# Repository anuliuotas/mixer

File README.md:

TODO:

### KiCad:
- MixerController: Bad mosfet footprint G and D pins are mixed up
- All: Mounting holes should be grounded
- All: Pinout should be visible at least in drawings layer

### ESPHome
- MixerController: VESC temperature sensor reading from CAN
- MixerInterface: Loading splash screen

### CAD
- Increase height of WAGO holder for more cable space

### Other
- Buy standoffs for VESC cover holder
- Check replacement parts

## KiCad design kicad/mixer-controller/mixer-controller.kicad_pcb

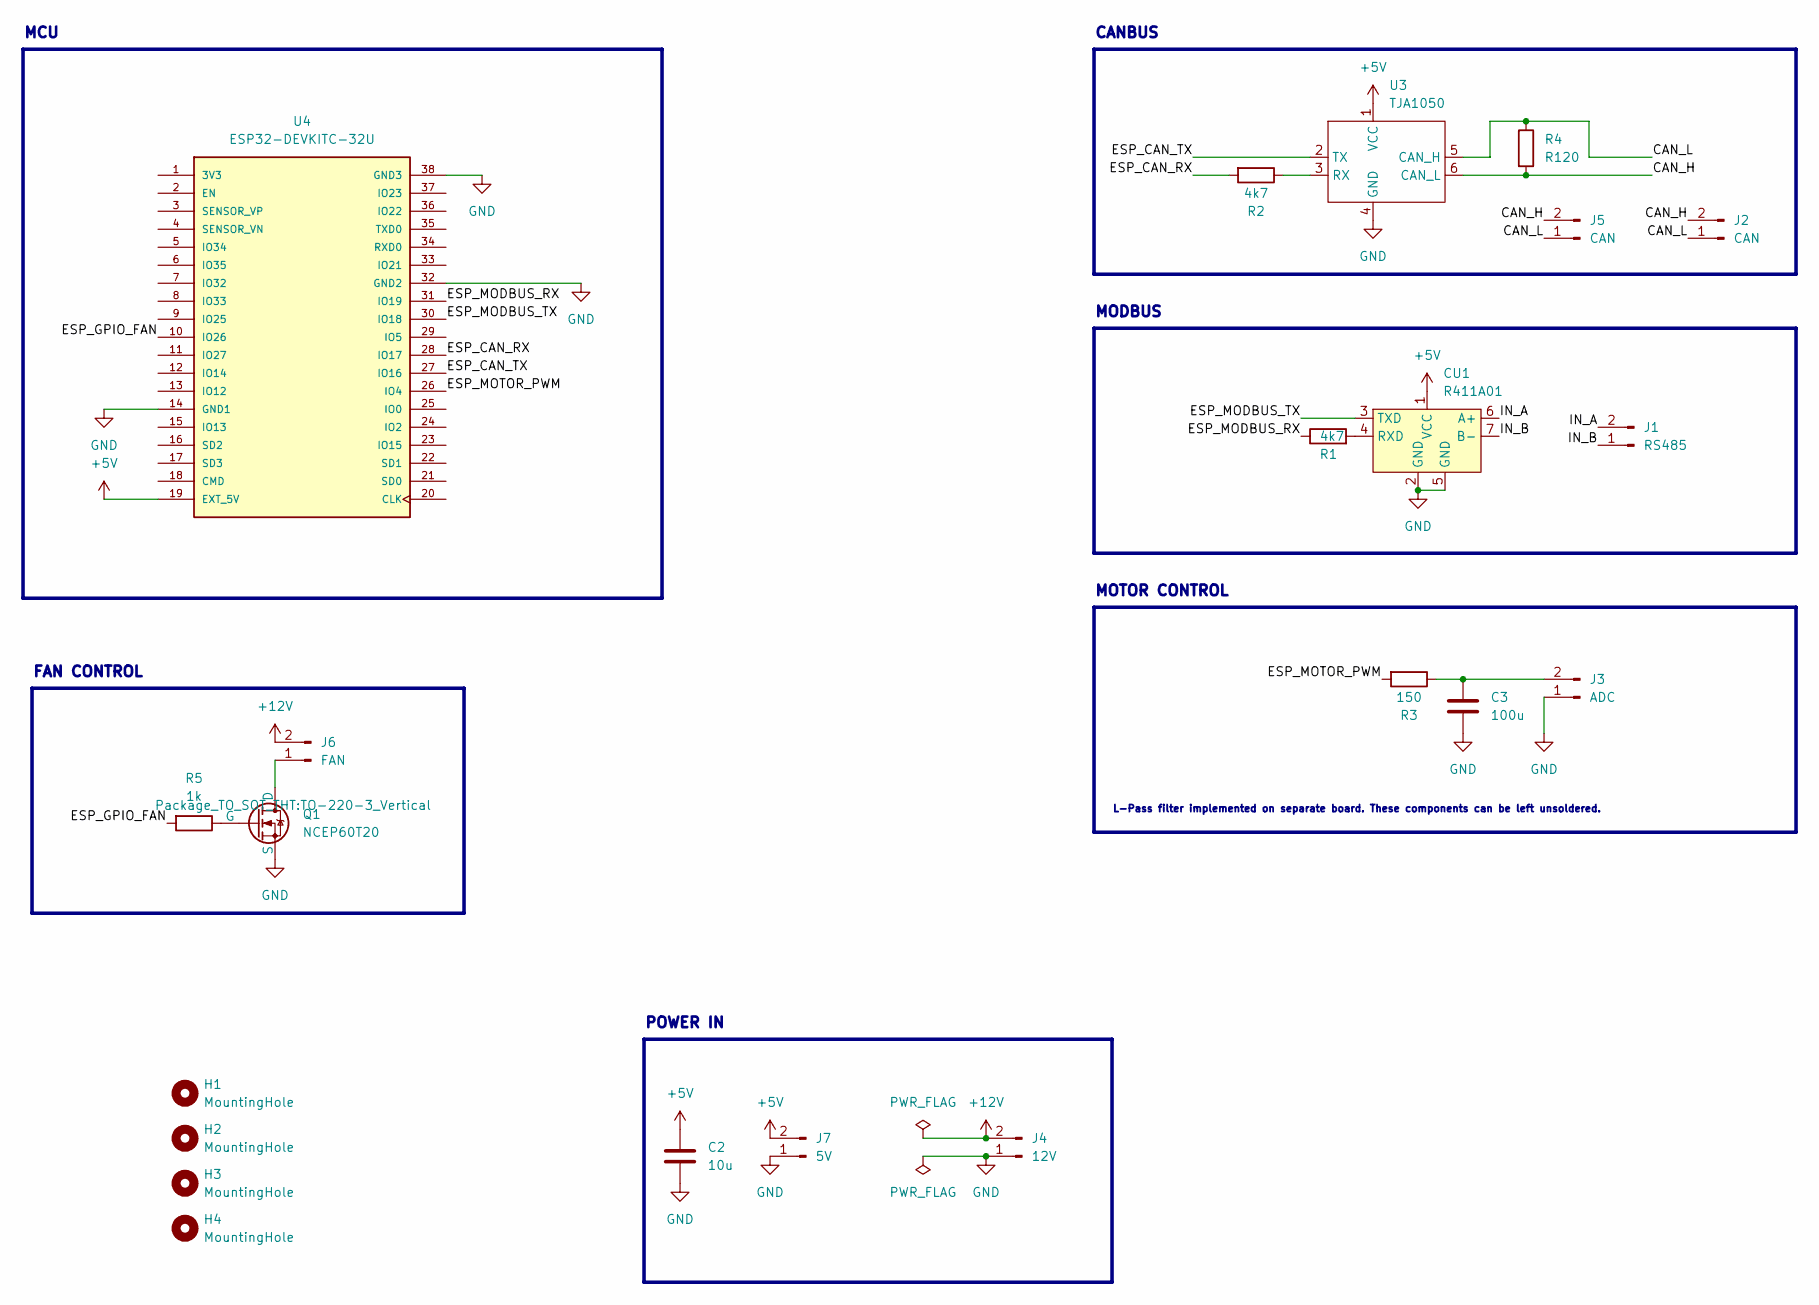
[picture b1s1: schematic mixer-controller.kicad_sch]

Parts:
C2: 10u; C_0805_2012Metric
C3: 100u; C_0805_2012Metric
CU1: R411A01
H1, H2, H3, H4: MountingHole; MountingHole_3.2mm_M3_Pad_Via
J1: RS485; JST_XH_B2B-XH-A_1x02_P2.50mm_Vertical
J2, J5: CAN; JST_XH_B2B-XH-A_1x02_P2.50mm_Vertical
J3: ADC; JST_XH_B2B-XH-A_1x02_P2.50mm_Vertical
J4: 12V; JST_XH_B2B-XH-A_1x02_P2.50mm_Vertical
J6: FAN; JST_XH_B2B-XH-A_1x02_P2.50mm_Vertical
J7: 5V; JST_XH_B2B-XH-A_1x02_P2.50mm_Vertical
Q1: NCEP60T20; TO-220-3_Vertical
R1: 4k7; R_0805_2012Metric
R2: 4k7; R_0805_2012Metric_Pad1.20x1.40mm_HandSolder
R3: 150; R_0805_2012Metric_Pad1.20x1.40mm_HandSolder
R4: R120; R_0805_2012Metric_Pad1.20x1.40mm_HandSolder
R5: 1k; R_0805_2012Metric_Pad1.20x1.40mm_HandSolder
U3: TJA1050
U4: ESP32-DEVKITC-32U; MODULE_ESP32-DEVKITC-32U; PARTREV N/A

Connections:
+5V: C2.1, CU1.1 (VCC), J7.2, U3.1 (VCC), U4.19 (EXT_5V)
+12V: J4.2, J6.2
/CAN_H: J2.2, J5.2, R4.2, U3.6 (CAN_L)
/CAN_L: J2.1, J5.1, R4.1, U3.5 (CAN_H)
/ESP_CAN_RX: R2.2, U4.28 (IO17)
/ESP_CAN_TX: U3.2 (TX), U4.27 (IO16)
/ESP_GPIO_FAN: R5.2, U4.10 (IO26)
/ESP_MODBUS_RX: R1.1, U4.31 (IO19)
/ESP_MODBUS_TX: CU1.3 (TXD), U4.30 (IO18)
/ESP_MOTOR_PWM: R3.2, U4.26 (IO4)
/IN_A: CU1.6 (A+), J1.2
/IN_B: CU1.7 (B-), J1.1
GND: C2.2, C3.2, CU1.2 (GND), CU1.5 (GND), J3.1, J4.1, J7.1, Q1.3 (S), U3.4 (GND), U4.14 (GND1), U4.32 (GND2), U4.38 (GND3)
unnamed: CU1.4 (RXD), R1.2
unnamed: C3.1, J3.2, R3.1
unnamed: J6.1, Q1.1 (D)
unnamed: Q1.2 (G), R5.1
unnamed: R2.1, U3.3 (RX)

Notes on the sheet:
POWER IN
FAN CONTROL
MODBUS
MCU
MOTOR CONTROL
L-Pass filter implemented on separate board. These components can be left unsoldered.
CANBUS

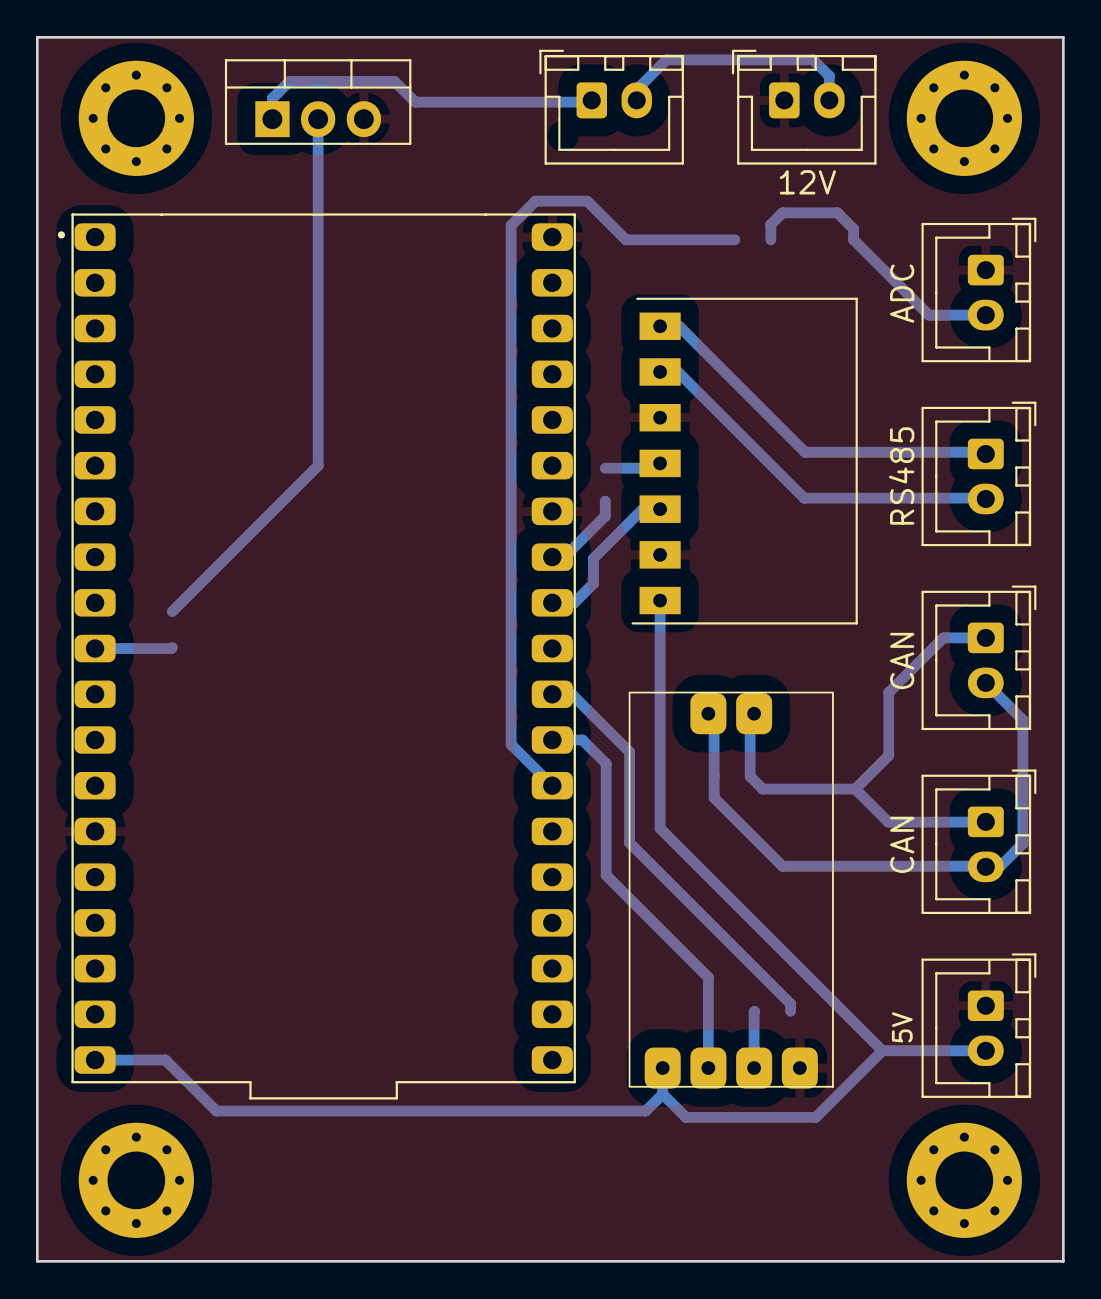
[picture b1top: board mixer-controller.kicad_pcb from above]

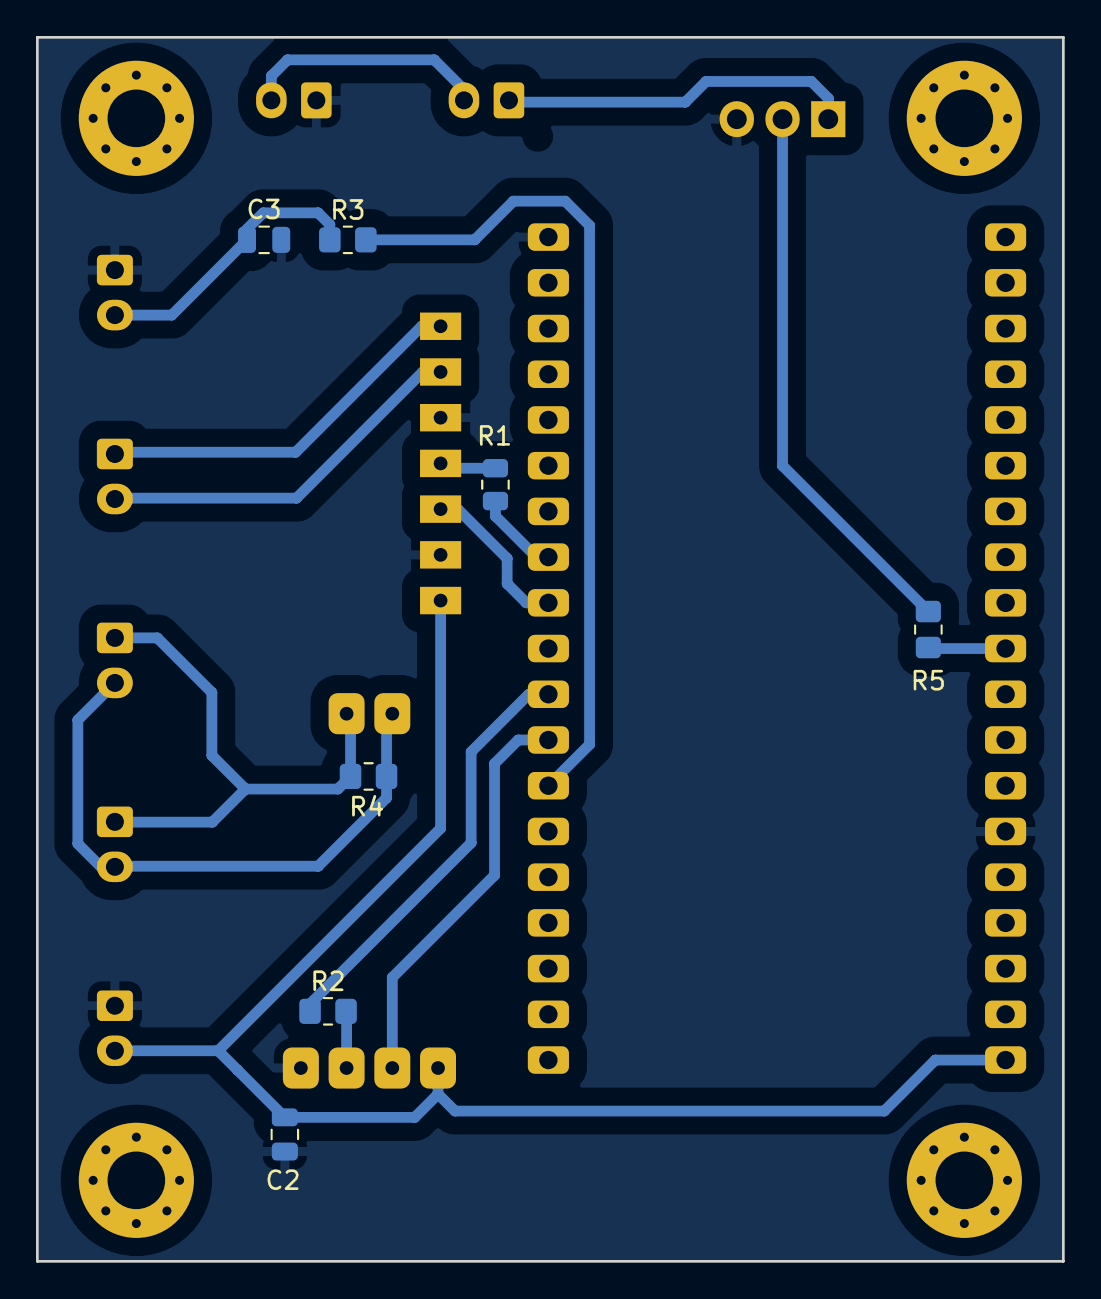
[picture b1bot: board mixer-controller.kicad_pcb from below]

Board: 2 copper layers, 57.0 x 68.0 mm, 22 parts (7 on the bottom side), 18 nets.

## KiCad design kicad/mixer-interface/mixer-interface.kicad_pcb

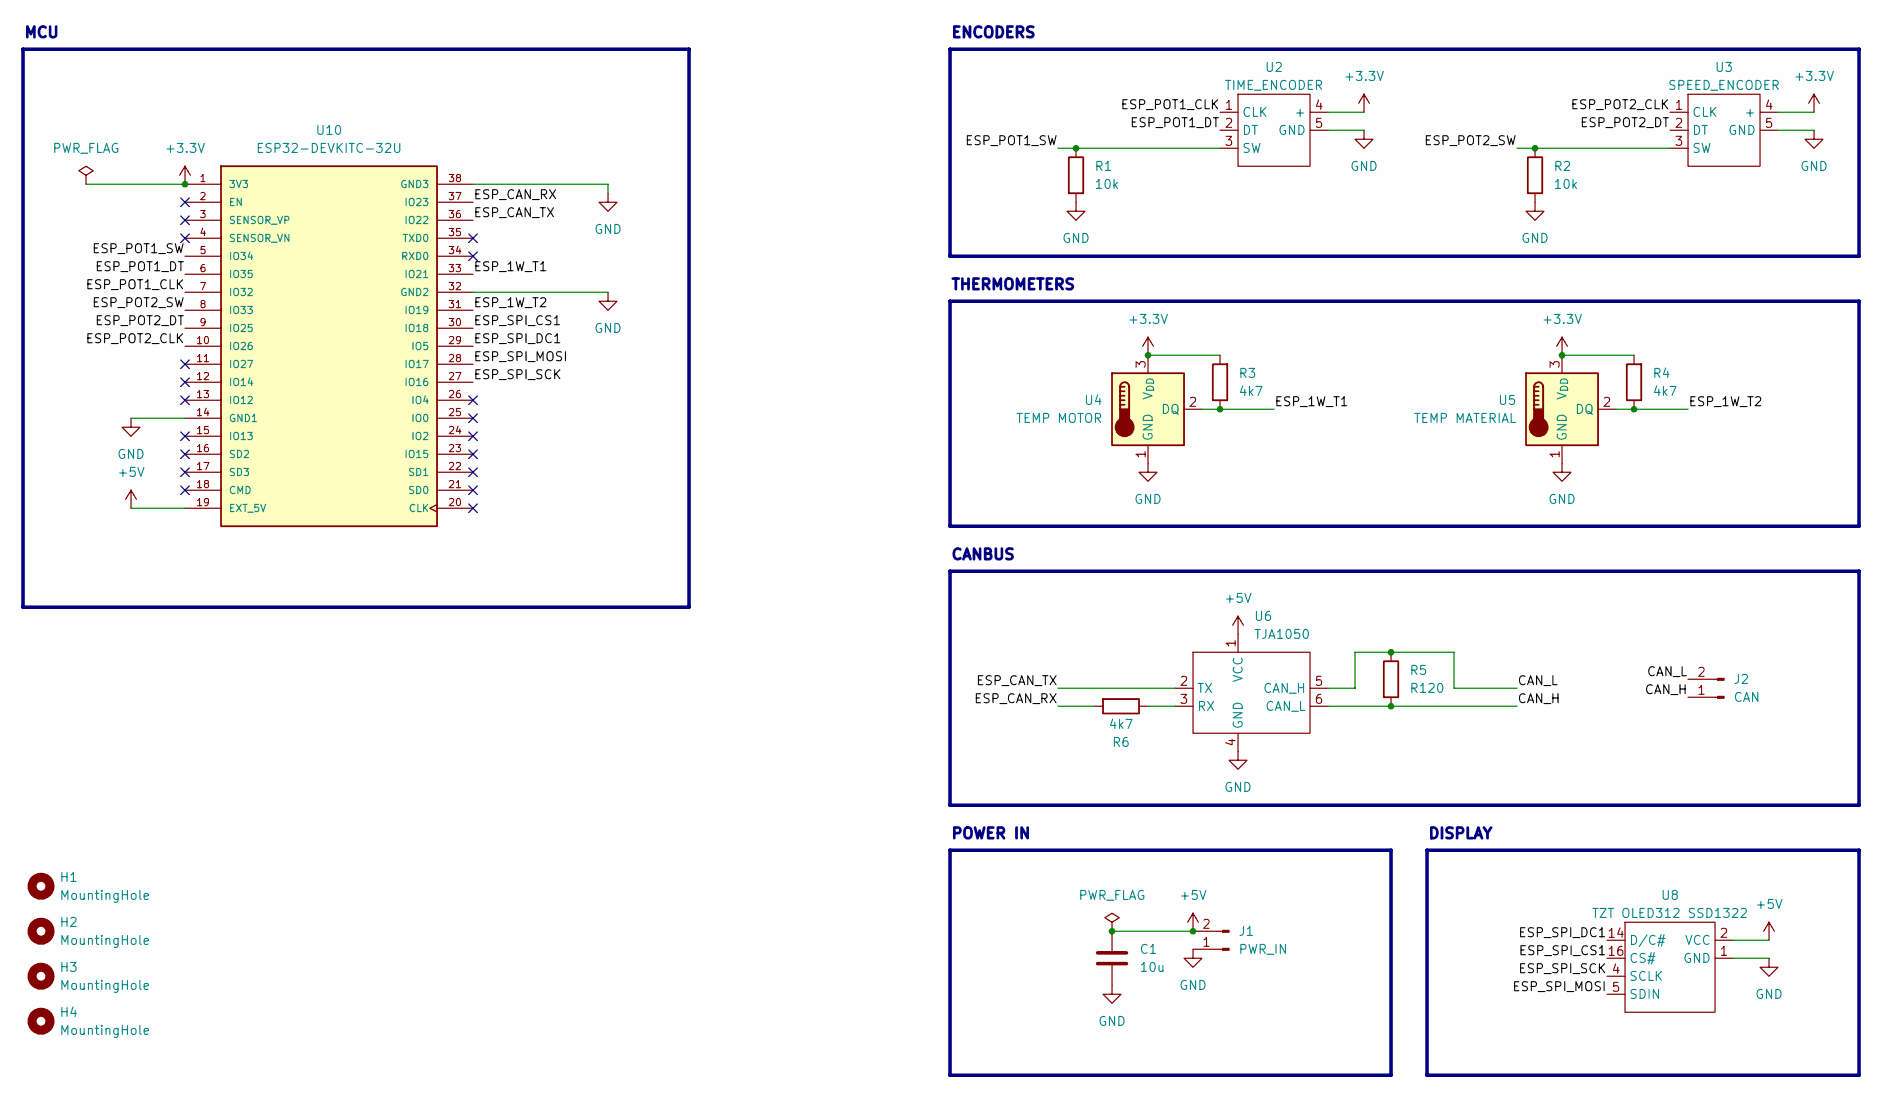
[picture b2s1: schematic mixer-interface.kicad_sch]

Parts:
C1: 10u; C_0805_2012Metric
H1, H2, H3, H4: MountingHole; MountingHole_3.2mm_M3_Pad_Via
J1: PWR_IN; JST_XH_B2B-XH-A_1x02_P2.50mm_Vertical
J2: CAN; JST_XH_B2B-XH-A_1x02_P2.50mm_Vertical
R1, R2: 10k; R_0805_2012Metric_Pad1.20x1.40mm_HandSolder
R3, R4, R6: 4k7; R_0805_2012Metric_Pad1.20x1.40mm_HandSolder
R5: R120; R_0805_2012Metric_Pad1.20x1.40mm_HandSolder
U2: TIME_ENCODER; JST_XH_B5B-XH-A_1x05_P2.50mm_Vertical
U3: SPEED_ENCODER; JST_XH_B5B-XH-A_1x05_P2.50mm_Vertical
U4: TEMP MOTOR; JST_XH_B3B-XH-A_1x03_P2.50mm_Vertical
U5: TEMP MATERIAL; JST_XH_B3B-XH-A_1x03_P2.50mm_Vertical
U6: TJA1050
U8: TZT OLED312 SSD1322; display_connector_jst_xh_6
U10: ESP32-DEVKITC-32U; MODULE_ESP32-DEVKITC-32U; PARTREV N/A

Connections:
+3.3V: R3.2, R4.2, U2.4 (+), U3.4 (+), U4.3 (V_{DD}), U5.3 (V_{DD}), U10.1 (3V3)
+5V: C1.1, J1.2, U6.1 (VCC), U8.2 (VCC), U10.19 (EXT_5V)
/CAN_H: J2.1, R5.2, U6.6 (CAN_L)
/CAN_L: J2.2, R5.1, U6.5 (CAN_H)
/ESP_1W_T1: R3.1, U4.2 (DQ), U10.33 (IO21)
/ESP_1W_T2: R4.1, U5.2 (DQ), U10.31 (IO19)
/ESP_CAN_RX: R6.2, U10.37 (IO23)
/ESP_CAN_TX: U6.2 (TX), U10.36 (IO22)
/ESP_POT1_CLK: U2.1 (CLK), U10.7 (IO32)
/ESP_POT1_DT: U2.2 (DT), U10.6 (IO35)
/ESP_POT1_SW: R1.1, U2.3 (SW), U10.5 (IO34)
/ESP_POT2_CLK: U3.1 (CLK), U10.10 (IO26)
/ESP_POT2_DT: U3.2 (DT), U10.9 (IO25)
/ESP_POT2_SW: R2.1, U3.3 (SW), U10.8 (IO33)
/ESP_SPI_CS1: U8.16 (CS#), U10.30 (IO18)
/ESP_SPI_DC1: U8.14 (D/C#), U10.29 (IO5)
/ESP_SPI_MOSI: U8.5 (SDIN), U10.28 (IO17)
/ESP_SPI_SCK: U8.4 (SCLK), U10.27 (IO16)
GND: C1.2, J1.1, R1.2, R2.2, U2.5 (GND), U3.5 (GND), U4.1 (GND), U5.1 (GND), U6.4 (GND), U8.1 (GND), U10.14 (GND1), U10.32 (GND2), U10.38 (GND3)
unnamed: R6.1, U6.3 (RX)

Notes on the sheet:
CANBUS
DISPLAY
MCU
POWER IN
THERMOMETERS
ENCODERS

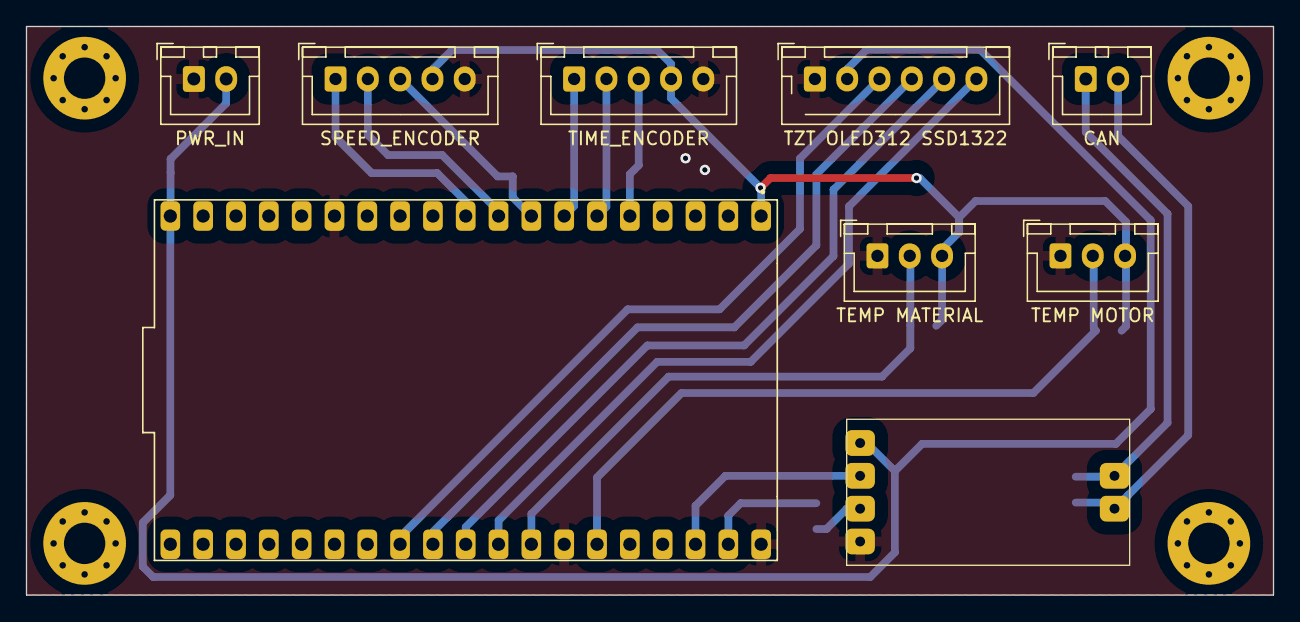
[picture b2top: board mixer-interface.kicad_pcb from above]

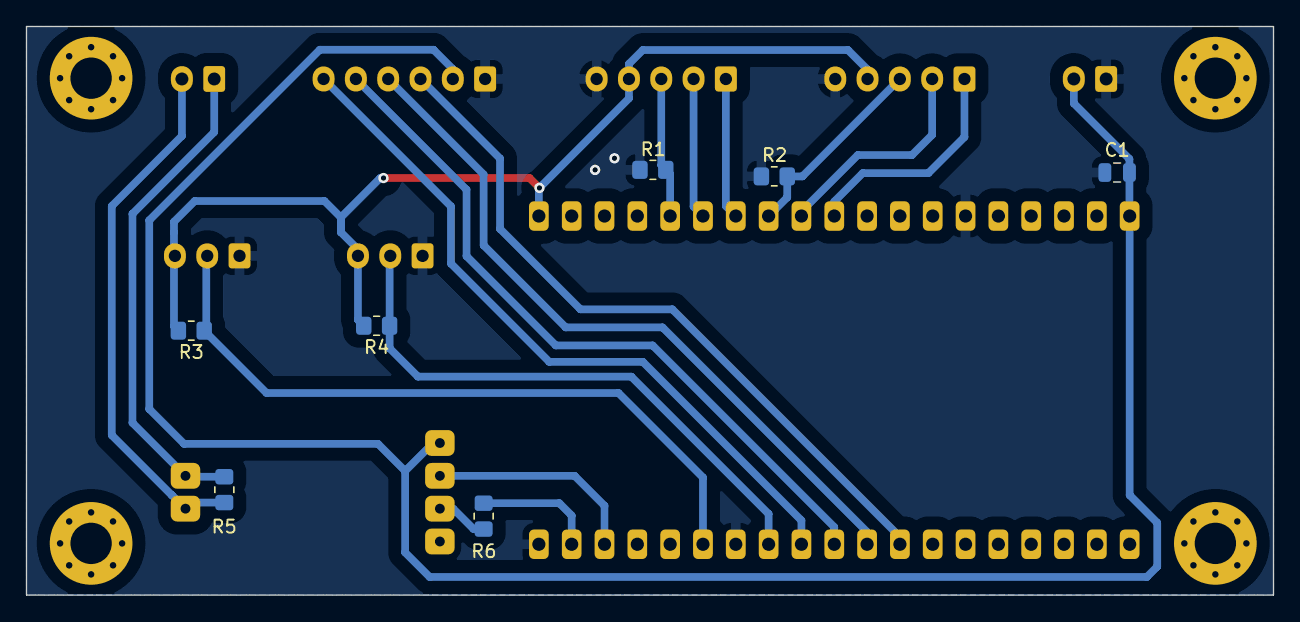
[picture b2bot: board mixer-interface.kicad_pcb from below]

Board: 2 copper layers, 96.5 x 44.0 mm, 20 parts (7 on the bottom side), 20 nets.

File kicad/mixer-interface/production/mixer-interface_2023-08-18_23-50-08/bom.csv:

Designator,Footprint,Quantity,Value,LCSC Part #
C1,0805,1,10u,
"H1, H2, H3, H4",MountingHole_3.2mm_M3_Pad_Via,4,MountingHole,
J1,JST_XH_B2B-XH-AM_1x02_P2.50mm_Vertical,1,PWR_IN,
J2,JST_XH_B2B-XH-AM_1x02_P2.50mm_Vertical,1,CAN,
"R1, R2",0805,2,10k,
"R3, R4, R6",0805,3,4k7,
R5,0805,1,R120,
U10,MODULE_ESP32-DEVKITC-32U,1,ESP32-DEVKITC-32U,
U2,JST_XH_B5B-XH-AM_1x05_P2.50mm_Vertical,1,TIME_ENCODER,
U3,JST_XH_B5B-XH-AM_1x05_P2.50mm_Vertical,1,SPEED_ENCODER,
U4,JST_XH_B3B-XH-AM_1x03_P2.50mm_Vertical,1,TEMP MOTOR,
U5,JST_XH_B3B-XH-AM_1x03_P2.50mm_Vertical,1,TEMP MATERIAL,
U6,TJA1050,1,TJA1050,
U8,display_connector_jst_xh_6,1,TZT OLED312 SSD1322,

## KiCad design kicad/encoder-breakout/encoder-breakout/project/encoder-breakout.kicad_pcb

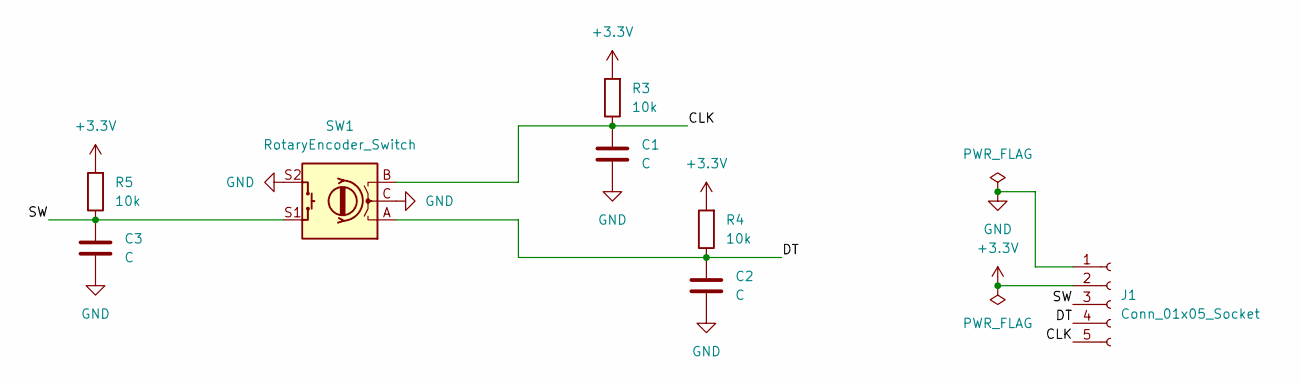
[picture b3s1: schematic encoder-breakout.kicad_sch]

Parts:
C1, C2, C3: C; C_0805_2012Metric_Pad1.18x1.45mm_HandSolder
J1: Conn_01x05_Socket; JST_XH_S5B-XH-A_1x05_P2.50mm_Horizontal
R3, R4, R5: 10k; R_0805_2012Metric_Pad1.20x1.40mm_HandSolder
SW1: RotaryEncoder_Switch; RotaryEncoder_Alps_EC11E-Switch_Vertical_H20mm

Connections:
+3.3V: J1.2, R3.2, R4.2, R5.2
/CLK: C1.1, J1.5, R3.1, SW1.B
/DT: C2.1, J1.4, R4.1, SW1.A
/SW: C3.1, J1.3, R5.1, SW1.S1
GND: C1.2, C2.2, C3.2, J1.1, SW1.C, SW1.S2

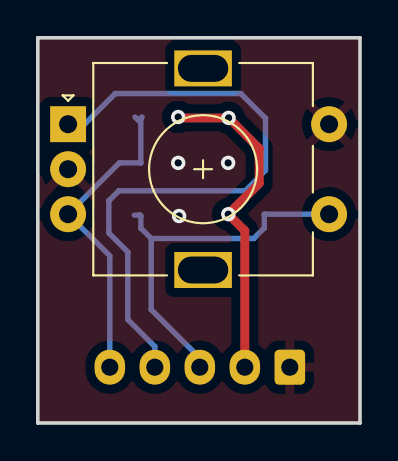
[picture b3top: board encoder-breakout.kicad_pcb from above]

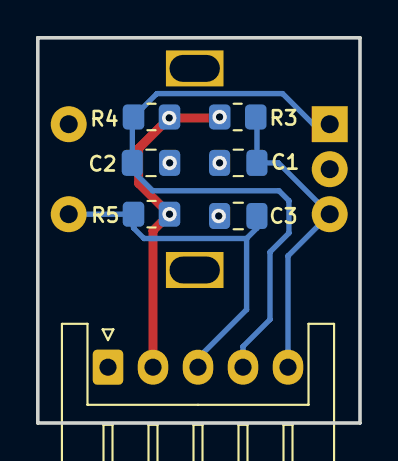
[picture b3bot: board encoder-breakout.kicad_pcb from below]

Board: 2 copper layers, 17.9 x 21.4 mm, 8 parts (7 on the bottom side), 5 nets.

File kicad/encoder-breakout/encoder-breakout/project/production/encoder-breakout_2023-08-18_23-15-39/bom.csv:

Designator,Footprint,Quantity,Value,LCSC Part #
"C1, C2, C3",0805,3,C,
J1,JST_XH_S5B-XH-A_1x05_P2.50mm_Horizontal,1,Conn_01x05_Socket,
"R3, R4, R5",0805,3,10k,
SW1,RotaryEncoder_Alps_EC11E-Switch_Vertical_H20mm,1,RotaryEncoder_Switch,

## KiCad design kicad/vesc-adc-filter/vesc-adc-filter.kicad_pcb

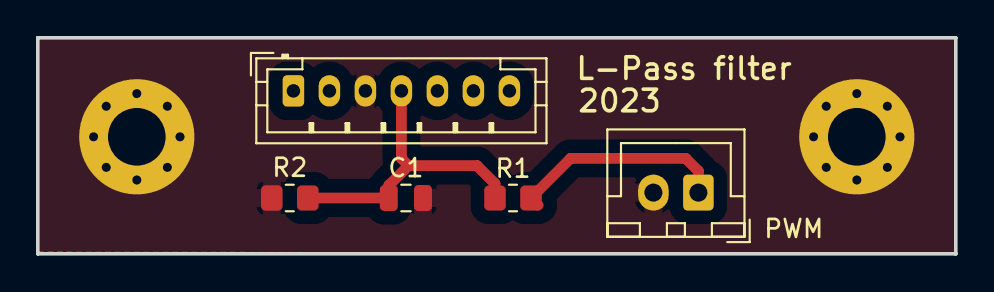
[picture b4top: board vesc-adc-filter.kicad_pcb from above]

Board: 2 copper layers, 51.0 x 12.0 mm, 7 parts (0 on the bottom side), 3 nets.

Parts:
C1: 100u; C_0805_2012Metric
H1, H2: MountingHole; MountingHole_3.2mm_M3_Pad_Via
J1: PWM; JST_XH_B2B-XH-A_1x02_P2.50mm_Vertical
R1: 150; R_0805_2012Metric_Pad1.20x1.40mm_HandSolder
R2: 100k; R_0805_2012Metric_Pad1.20x1.40mm_HandSolder
U1: JST_PH_B7B-PH-K_1x07_P2.00mm_Vertical

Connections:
GND: C1.2, J1.2, R2.2, U1.3 (GND)
unnamed: J1.1, R1.2
unnamed: C1.1, R1.1, R2.1, U1.4 (ADC1)

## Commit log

2023-08-14 Initial commit of the project
2023-08-15 Added separate PCB for VESC ADC L-pass filter
2023-08-18 Added encoder breakout and updated other projects
2023-08-22 Final updates for manufacturing
2023-09-02 Changes after manufacting
2023-11-21 Added PZEM and MQQT config
2023-11-21 Added readme with todo list
2023-11-21 Fixed readme formatting
2024-01-19 Negative measured speed RPM values are replaces as zero in the interface
2024-01-19 Switched encoder places
